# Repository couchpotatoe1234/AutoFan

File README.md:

# AutoFan
One day, it was really hot and I was sitting at my computer, programming, when I decided to reach over to turn on my desktop fan. As I did that, I realized, why don't I just automate this so I can focus more on my projects now? So here it is: the AutoFan that turns on when over a certain temperature and when a human is detected.

(my case)

(my PCB)

| Name                | Purpose                                             | Quantity | Total Cost (USD) | Link                                                                                                                                                                                                                                                                     | Distributor |
|---------------------|-----------------------------------------------------|----------|------------------|--------------------------------------------------------------------------------------------------------------------------------------------------------------------------------------------------------------------------------------------------------------------------|-------------|
| PCB                 | its the Printed Circuit Board                       | 1        | 6.90             | https://cart.jlcpcb.com/shopcart/cart/                                                                                                                                                                                                                                   | JLCPCB      |
| RM2X12MM 2701       | some M2 screws to hold everything together          | 8        | 5.70             | https://www.digikey.com/en/products/detail/apm-hexseal/RM2X12MM-2701/3712290                                                                                                                                                                                             | Digikey     |
| PH1-07-UA           | these are the 7 pin headers for the microcontroller | 2        | 0.20             | https://www.digikey.com/en/products/detail/adam-tech/PH1-07-UA/9830505                                                                                                                                                                                                   | Digikey     |
| MF30060V1-1000U-A99 | this is the 30mmx30mm fan that I will be using      | 1        | 6.92             | https://www.digikey.com/en/products/detail/sunon-fans/MF30060V1-1000U-A99/10441401                                                                                                                                                                                       | Digikey     |
| 4871                | this is the PIR sensor                              | 1        | 3.95             | https://www.digikey.com/en/products/detail/adafruit-industries-llc/4871/13922055?_gl=1*olxfgm*_up*MQ..*_gs*NA..&gclid=CjwKCAjw-J3OBhBuEiwAwqZ_hxuGVZsPxHF1e7pHXbn-eyiwHbPT6YZBRWRSUoa_rMKD0nDpZSkZZxoCS80QAvD_BwE&gclsrc=aw.ds&gbraid=0AAAAADrbLlibWss_wAgYhSjCoqfi9qAB0 | Digikey     |
| 2464                | this is the 3 AA battery holder                     | 1        | 1.77             | https://www.digikey.com/en/products/detail/keystone-electronics/2464/303813                                                                                                                                                                                              | Digikey     |
| TSW-103-07-F-S      | this is the 3 pin header for the motion sensor      | 1        | 0.17             | https://www.digikey.com/en/products/detail/samtec-inc/TSW-103-07-F-S/2685877                                                                                                                                                                                             | Digikey     |
| TSW-102-07-F-S      | this is the 2 pin header for the fan                | 1        | 0.11             | https://www.digikey.com/en/products/detail/samtec-inc/TSW-102-07-F-S/2685866                                                                                                                                                                                             | Digikey     |
| CF14JT220R          | 220Ω resistor                                       | 1        | 0.10             | https://www.digikey.com/en/products/detail/stackpole-electronics-inc/CF14JT220R/1741346                                                                                                                                                                                  | Digikey     |
| CF14JT4K70          | 4.7kΩ resistor                                      | 1        | 0.10             | https://www.digikey.com/en/products/detail/stackpole-electronics-inc/CF14JT4K70/1741428                                                                                                                                                                                  | Digikey     |
| 1N4001              | this is the diode                                   | 1        | 0.12             | https://www.digikey.com/en/products/detail/diotec-semiconductor/1N4001/13164614                                                                                                                                                                                          | Digikey     |
| TN0620N3-G          | the N-channel mosfet                                | 1        | 1.63             | https://www.digikey.com/en/products/detail/microchip-technology/TN0620N3-G/4902375                                                                                                                                                                                       | Digikey     |
| DS18B20+            | this is the heat sensor                             | 1        | 7.46             | https://www.digikey.com/en/products/detail/analog-devices-inc-maxim-integrated/DS18B20/956983                                                                                                                                                                            | Digikey     |
| 102010428           | This is the microcontroller, the seeed xiao rp2040  | 1        | 4.68             | https://www.digikey.com/en/products/detail/seeed-technology-co-ltd/102010428/14672129                                                                                                                                                                                    | Digikey     |

Onshape document: https://cad.onshape.com/documents/0db31313949541dd367d7870/w/98a7ab71d9118e1847d053de/e/f6c7b79dca7cdf03d4a1478a?renderMode=0&uiState=69cdbc9983360133a7f5effd

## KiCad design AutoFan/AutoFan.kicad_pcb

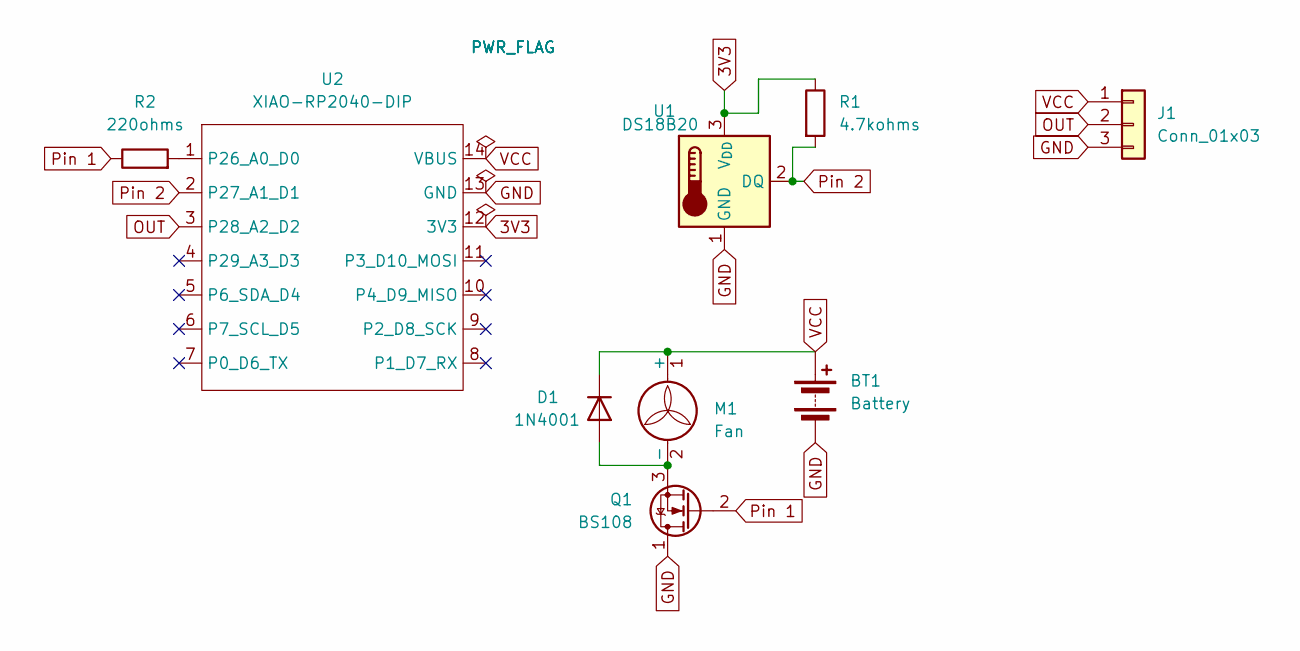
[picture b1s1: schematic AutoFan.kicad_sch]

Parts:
BT1: Battery; BatteryHolder_TruPower_BH-331P_3xAA
D1: 1N4001; D_DO-41_SOD81_P10.16mm_Horizontal
J1: Conn_01x03; PinHeader_1x03_P2.54mm_Vertical
M1: Fan; PinHeader_1x02_P2.54mm_Vertical
Q1: BS108; TO-92_Inline
R1: 4.7kohms; R_Axial_DIN0207_L6.3mm_D2.5mm_P7.62mm_Horizontal
R2: 220ohms; R_Axial_DIN0207_L6.3mm_D2.5mm_P7.62mm_Horizontal
U1: DS18B20; TO-92_Inline
U2: XIAO-RP2040-DIP; XIAO-Generic-Hybrid-14P-2.54-21X17.8MM

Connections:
3V3: R1.1, U1.3 (V_{DD}), U2.12 (3V3)
GND: BT1.2 (-), J1.3, Q1.1 (D), U1.1 (GND), U2.13 (GND)
unnamed: D1.2 (A), M1.2 (-), Q1.3 (S)
unnamed: R2.2, U2.1 (P26_A0_D0)
OUT: J1.2, U2.3 (P28_A2_D2)
Pin 1: Q1.2 (G), R2.1
Pin 2: R1.2, U1.2 (DQ), U2.2 (P27_A1_D1)
VCC: BT1.1 (+), D1.1 (K), J1.1, M1.1 (+), U2.14 (VBUS)

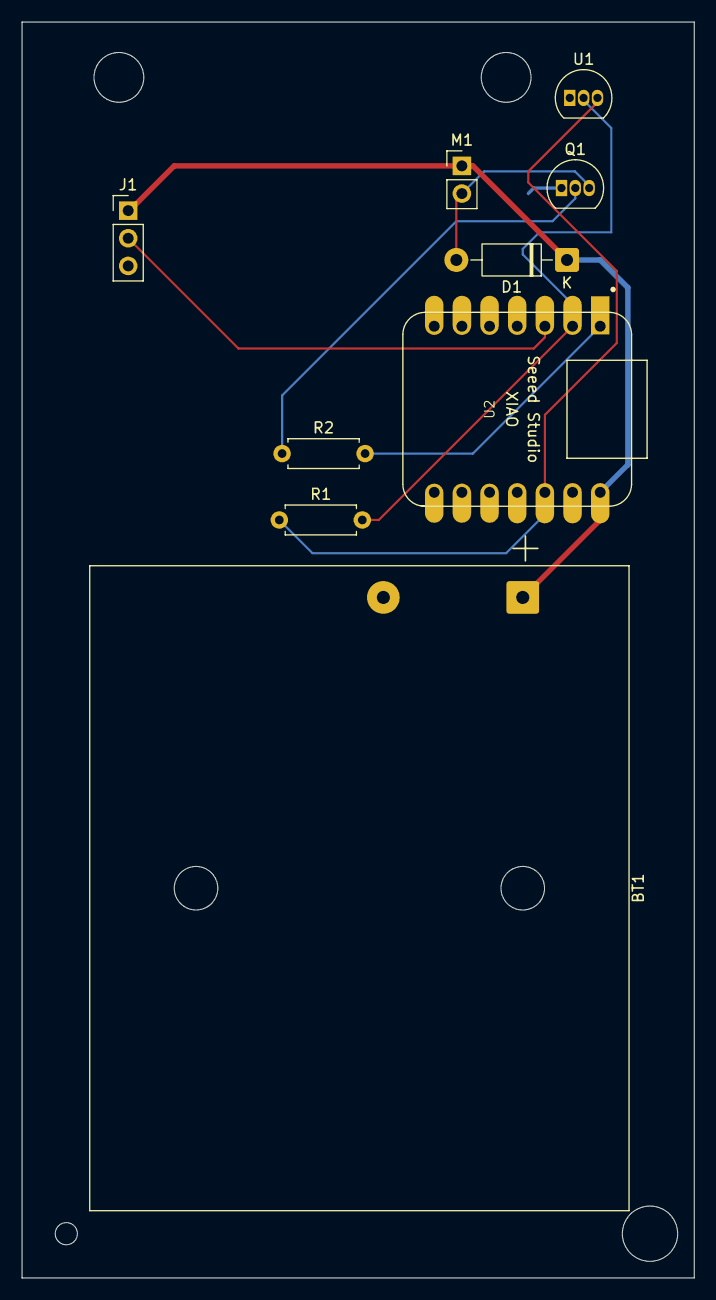
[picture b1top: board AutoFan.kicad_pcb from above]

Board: 2 copper layers, 61.7 x 115.3 mm, 9 parts (0 on the bottom side), 8 nets.

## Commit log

2026-04-01 some PCB stuff
2026-04-01 adding BOM
2026-04-02 Cad files
2026-04-03 firmware
2026-04-03 updated Firmware
2026-04-04 updating PCB
2026-04-04 new README
2026-04-04 images
2026-04-04 final README update
2026-04-05 finishing touches on PCB
